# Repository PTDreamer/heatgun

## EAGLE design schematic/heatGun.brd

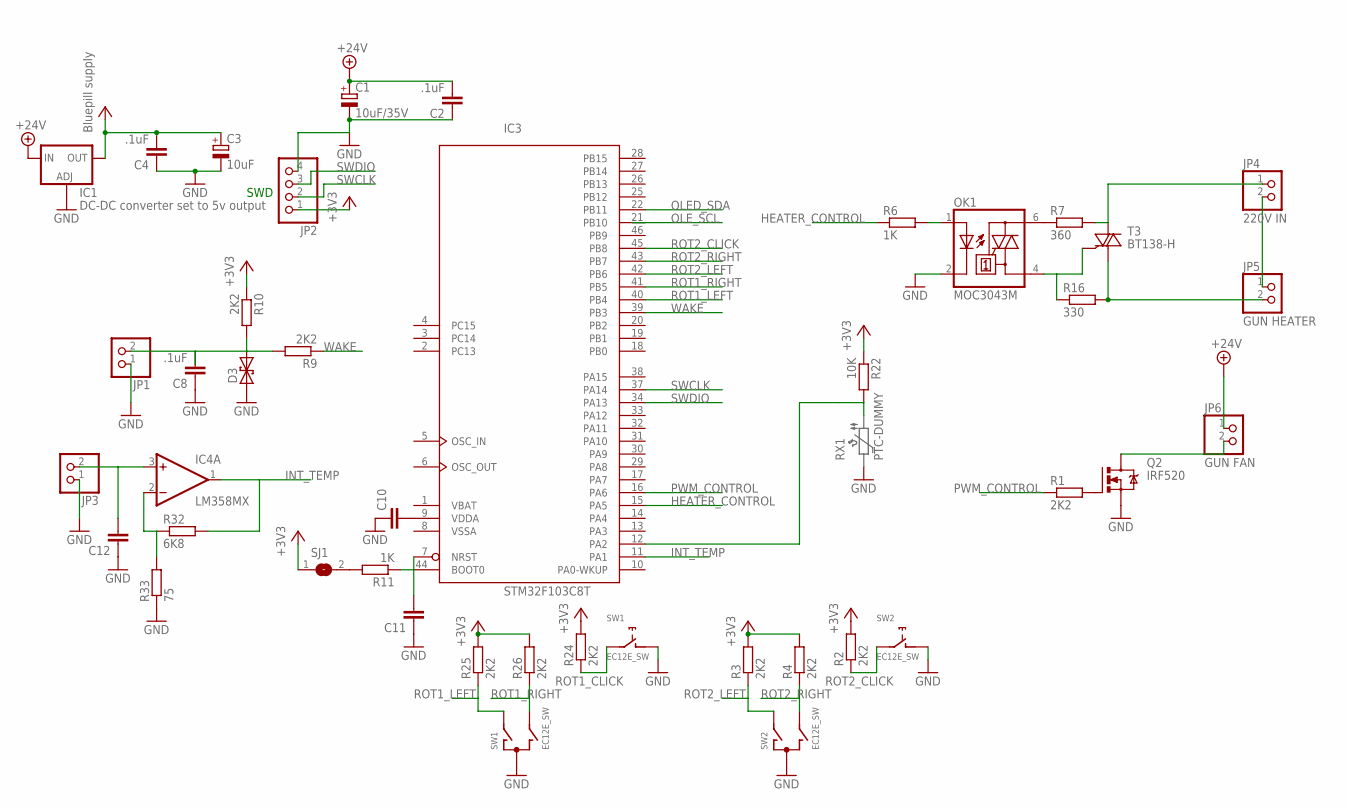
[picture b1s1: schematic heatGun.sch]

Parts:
C1: 10uF/35V; E2,5-6E
C2, C4, C8: .1uF; C0603
C3: 10uF; E2,5-6E
C10, C11, C12: C-EUC0603; C0603
D3: BZW04XXB; F126Z12
IC1: DC-DC converter set to 5v output; SOT223
IC3: STM32F103C8T; LQFP48
IC4: LM358MX; SO08
JP1, JP3: PINHD-1X2; 1X02
JP2: PINHD-1X4; 1X04
JP4: 220V IN; 1X02
JP5: GUN HEATER; 1X02
JP6: GUN FAN; 1X02
OK1: MOC3043M; DIL06
Q2: IRF520; TO220BV
R1, R2, R3, R4, R9, R10, R24, R25, R26: 2K2; R0603
R6, R11: 1K; R0603
R7: 360; R0603
R16: 330; R0603
R22: 10K; R0603
R32: 6K8; R0603
R33: 75; R0603
SJ1: SJ
SW1, SW2: EC12E_SW; ALPS_EC12E_SW
T3: BT138-H; TO220BH

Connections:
+3V3: C3.+, C4.2, IC1.4 (OUT), JP2.1, R2.2, R3.2, R4.2, R10.1, R22.1, R24.2, R25.2, R26.2, SJ1.1
+24V: C1.+, C2.2, IC1.3 (IN), JP6.1
GND: C1.-, C2.1, C3.-, C4.1, C8.1, C10.1, C11.1, C12.1, D3.A (1), IC1.1 (ADJ), JP1.1, JP2.4, JP3.1, OK1.2 (C), Q2.S, R33.1, SW1.C, SW1.D (1), SW2.C, SW2.D (1)
HEATER_CONTROL: IC3.15 (PA5), R6.1
INT_TEMP: IC3.11 (PA1), IC4.1 (OUT), R32.2
unnamed: Q2.G, R1.2
unnamed: JP6.2, Q2.D
unnamed: OK1.1 (A), R6.2
unnamed: IC3.44 (BOOT0), R11.1
unnamed: R11.2, SJ1.2
unnamed: C12.2, IC4.3 (+IN), JP3.2
unnamed: OK1.6 (A2), R7.1
unnamed: JP4.1, R7.2, T3.T2 (A2)
unnamed: IC3.12 (PA2), R22.2
unnamed: C10.2, IC3.9 (VDDA)
unnamed: C11.2, IC3.7 (NRST)
unnamed: OK1.4 (A1), R16.1, T3.G
unnamed: JP4.2, JP5.1
unnamed: JP5.2, R16.2, T3.T1 (A1)
unnamed: IC4.2 (-IN), R32.1, R33.2
OLED_SDA: IC3.22 (PB11)
OLE_SCL: IC3.21 (PB10)
PWM_CONTROL: IC3.16 (PA6), R1.1
REED: C8.2, D3.C (2), JP1.2, R9.2, R10.2
ROT1_CLICK: R24.1, SW1.E (2)
ROT1_LEFT: IC3.40 (PB4), R25.1, SW1.A
ROT1_RIGHT: IC3.41 (PB5), R26.1, SW1.B
ROT2_CLICK: IC3.45 (PB8), R2.1, SW2.E (2)
ROT2_LEFT: IC3.42 (PB6), R3.1, SW2.A
ROT2_RIGHT: IC3.43 (PB7), R4.1, SW2.B
SWCLK: IC3.37 (PA14), JP2.2
SWDIO: IC3.34 (PA13), JP2.3
V+: IC4.8 (V+)
V-: IC4.4 (V-)
VBAT: IC3.1 (VBAT)
VDD: IC3.24 (VDD), IC3.36 (VDD), IC3.48 (VDD)
VSS: IC3.23 (VSS), IC3.35 (VSS), IC3.47 (VSS)
VSSA: IC3.8 (VSSA)
WAKE: IC3.39 (PB3), R9.1

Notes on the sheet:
SWD

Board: 2 copper layers, 40 parts (0 on the bottom side), 33 nets, no tracks yet.

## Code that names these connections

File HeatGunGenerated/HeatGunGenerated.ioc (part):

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Mcu.Name=STM32F103C(8-B)Tx
Mcu.Package=LQFP48
Mcu.UserName=STM32F103C8Tx
PA1.GPIOParameters=GPIO_Label
PA1.GPIO_Label=GUN TEMP
PA1.Signal=ADCx_IN1
PA10.Mode=Asynchronous
PA10.Signal=USART1_RX
PA13.Mode=Serial_Wire
PA13.Signal=SYS_JTMS-SWDIO
PA14.Mode=Serial_Wire
PA14.Signal=SYS_JTCK-SWCLK
PA2.GPIOParameters=GPIO_Label
PA2.GPIO_Label=NTC
PA2.Signal=ADCx_IN2
PA3.GPIOParameters=GPIO_Label
PA3.GPIO_Label=VIN
PA3.Signal=ADCx_IN3
PA5.GPIOParameters=GPIO_Speed,GPIO_Label
PA5.GPIO_Label=HEATER_CONTROL
PA5.GPIO_Speed=GPIO_SPEED_FREQ_HIGH
PA5.Signal=GPIO_Output
PA6.GPIOParameters=GPIO_Label
PA6.GPIO_Label=PWM_FAN_CONTROL
PA6.Signal=S_TIM3_CH1
PA9.Mode=Asynchronous
PA9.Signal=USART1_TX
PB10.Mode=I2C
PB10.Signal=I2C2_SCL
PB11.Mode=I2C
PB11.Signal=I2C2_SDA
PB3.GPIOParameters=GPIO_PuPd,GPIO_Label,GPIO_ModeDefaultEXTI
PB3.GPIO_Label=WAKE
PB3.GPIO_ModeDefaultEXTI=GPIO_MODE_IT_RISING_FALLING
PB3.GPIO_PuPd=GPIO_PULLUP
PB3.Signal=GPXTI3
PB4.GPIOParameters=GPIO_Label,GPIO_ModeDefaultEXTI
PB4.GPIO_Label=ROT1_LEFT
PB4.GPIO_ModeDefaultEXTI=GPIO_MODE_IT_RISING_FALLING
PB4.Signal=GPXTI4
PB5.GPIOParameters=GPIO_Label,GPIO_ModeDefaultEXTI
PB5.GPIO_Label=ROT1_RIGHT
PB5.GPIO_ModeDefaultEXTI=GPIO_MODE_IT_RISING_FALLING
PB5.Signal=GPXTI5
PB6.GPIOParameters=GPIO_Label,GPIO_ModeDefaultEXTI
PB6.GPIO_Label=ROT1_CLICK
PB6.GPIO_ModeDefaultEXTI=GPIO_MODE_IT_RISING_FALLING
PB6.Signal=GPXTI6
PB7.GPIOParameters=GPIO_Label,GPIO_ModeDefaultEXTI
PB7.GPIO_Label=ROT2_LEFT
PB7.GPIO_ModeDefaultEXTI=GPIO_MODE_IT_RISING_FALLING
PB7.Signal=GPXTI7
PB8.GPIOParameters=GPIO_Label,GPIO_ModeDefaultEXTI
PB8.GPIO_Label=ROT2_RIGHT
PB8.GPIO_ModeDefaultEXTI=GPIO_MODE_IT_RISING_FALLING
PB8.Signal=GPXTI8
PB9.GPIOParameters=GPIO_Label,GPIO_ModeDefaultEXTI
PB9.GPIO_Label=ROT2_CLICK
PB9.GPIO_ModeDefaultEXTI=GPIO_MODE_IT_RISING_FALLING
PB9.Signal=GPXTI9
PC13-TAMPER-RTC.GPIOParameters=GPIO_Label
PC13-TAMPER-RTC.GPIO_Label=LED
PC13-TAMPER-RTC.Signal=GPIO_Output
PC14-OSC32_IN.Mode=LSE-External-Oscillator
PC14-OSC32_IN.Signal=RCC_OSC32_IN
PC15-OSC32_OUT.Mode=LSE-External-Oscillator
PC15-OSC32_OUT.Signal=RCC_OSC32_OUT
PD0-OSC_IN.Mode=HSE-External-Oscillator
PD0-OSC_IN.Signal=RCC_OSC_IN
PD1-OSC_OUT.Mode=HSE-External-Oscillator
PD1-OSC_OUT.Signal=RCC_OSC_OUT
RCC.HSEDivPLL=RCC_HSE_PREDIV_DIV2
RCC.SYSCLKFreq_VALUE=48000000
RCC.SYSCLKSource=RCC_SYSCLKSOURCE_PLLCLK
board=HeatGunGenerated

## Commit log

2017-11-03 latest fixes
2017-11-05 misc file adds
2017-11-05 gitignore ignore .settings
2018-02-08 cleaning
2018-06-07 Updated schematic
2018-06-07 Made last settings prevail
